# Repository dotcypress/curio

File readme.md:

# Curio

Glorified Infrared Remote Control.

## Resources

- [Schematics](docs/curio.pdf)
- [Gerber files](docs/curio_pcb_rev_0x02.zip)
- [Interactive BOM](https://htmlpreview.github.io/?https://github.com/dotcypress/curio/blob/main/docs/ibom.html)
- [Rust firmware](https://github.com/dotcypress/curio-firmware)

## Credits

* [`1-Bit Icons`](https://vectorpixelstar.itch.io) by VectorPixelStar
* [`Edition 12`](https://www.dafont.com/edition-12.font) font by Designer's High
* [`BM Army`](https://www.dafont.com/bm-army.font) font by BitmapMania
* [`Nokia Cellphone FC`](https://www.dafont.com/nokia-cellphone.font) font by Zeh Fernando

## License

Licensed under either of

- Apache License, Version 2.0 ([LICENSE-APACHE](LICENSE-APACHE) or
  http://www.apache.org/licenses/LICENSE-2.0)
- MIT license ([LICENSE-MIT](LICENSE-MIT) or http://opensource.org/licenses/MIT)

at your option.

### Contribution

Unless you explicitly state otherwise, any contribution intentionally submitted
for inclusion in the work by you, as defined in the Apache-2.0 license, shall be
dual licensed as above, without any additional terms or conditions.

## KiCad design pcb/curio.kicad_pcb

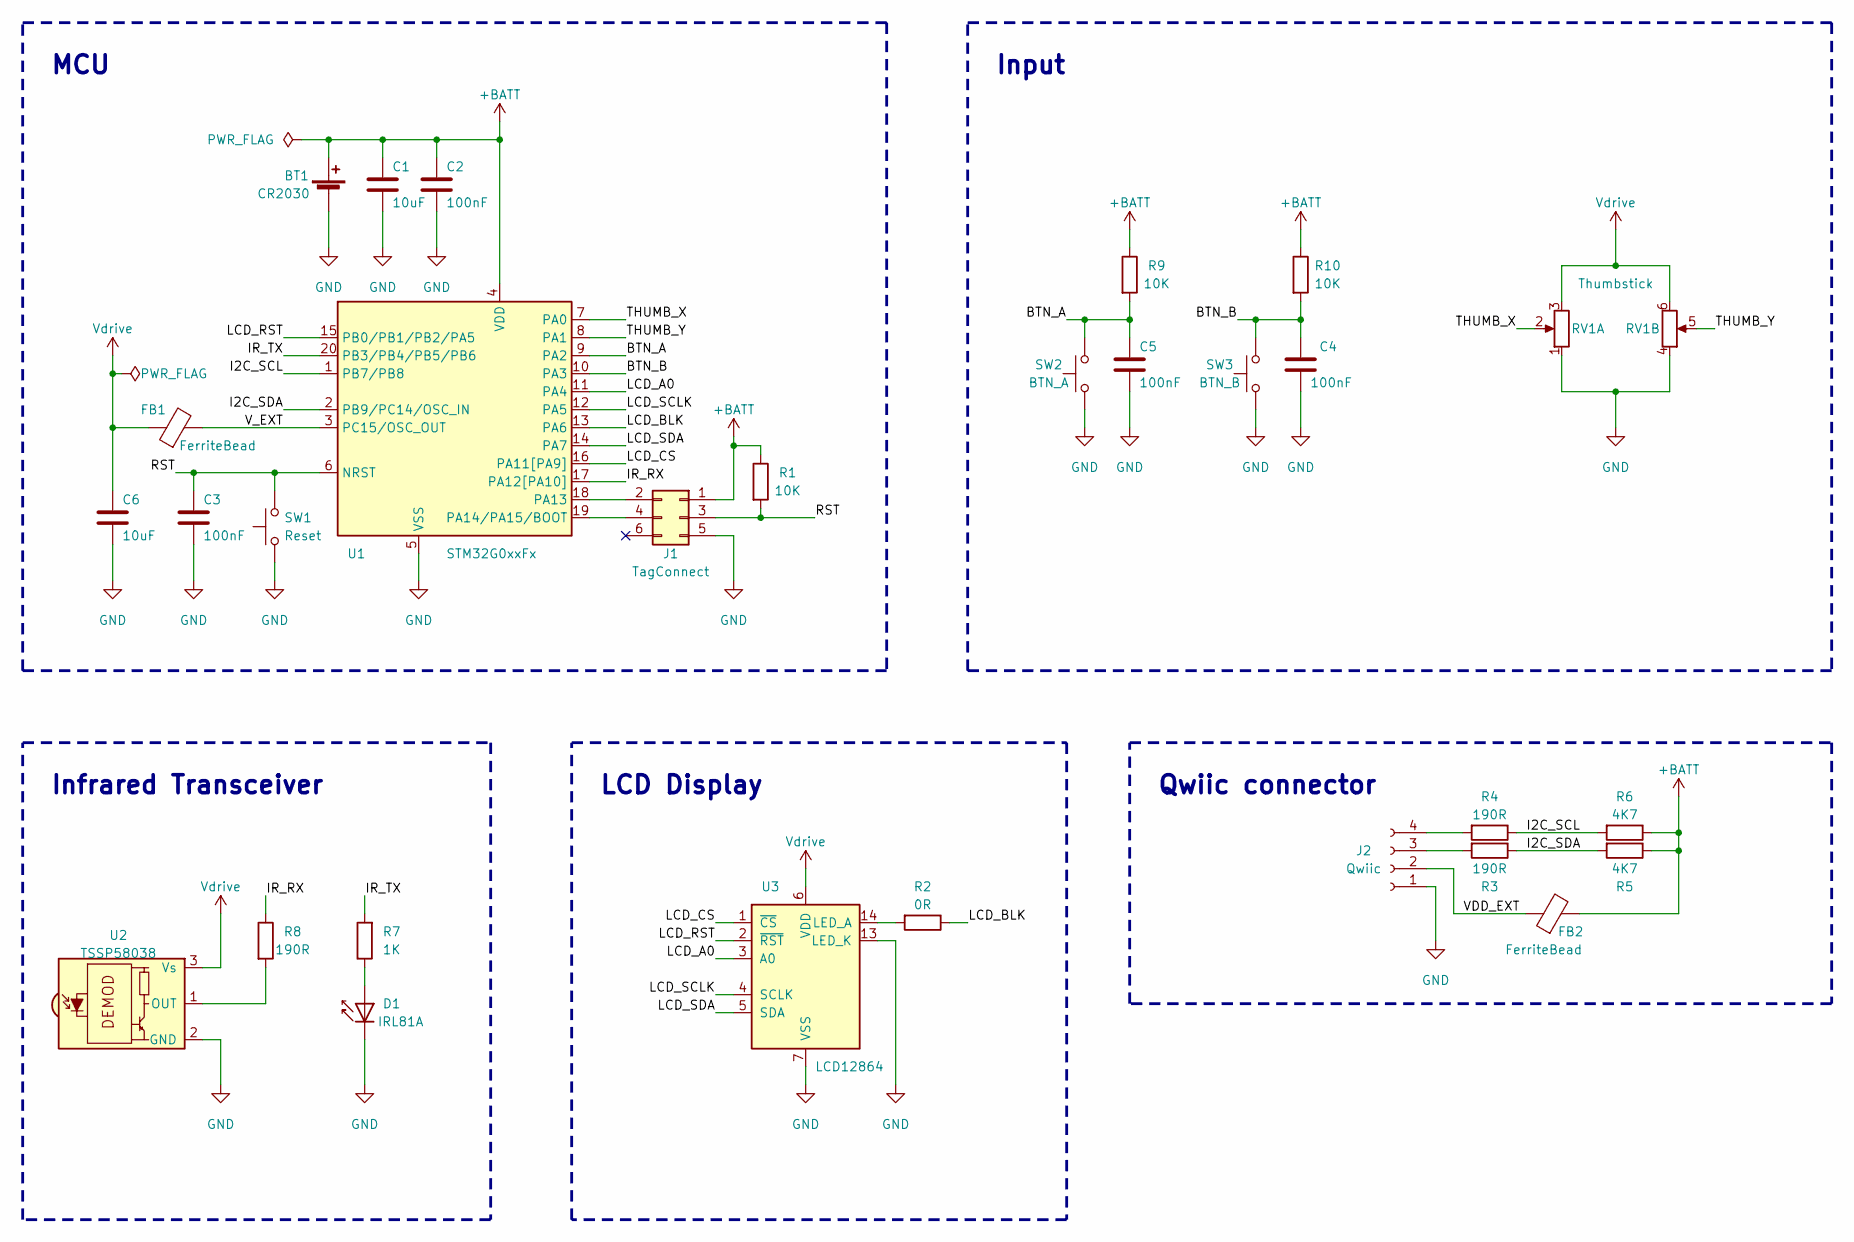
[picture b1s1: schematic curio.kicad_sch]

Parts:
BT1: CR2030; BatteryHolder-Lynx-BAT-HLD-001
C1, C6: 10uF; C_0603_1608Metric
C2, C3, C4, C5: 100nF; C_0603_1608Metric
D1: IRL81A; LED_SideEmitter_Rectangular_W4.5mm_H1.6mm
FB1, FB2: FerriteBead; R_0603_1608Metric
J1: TagConnect; Tag-Connect_TC2030-IDC-NL_2x03_P1.27mm_Vertical
J2: Qwiic; JST_SH_SM04B-SRSS-TB_1x04-1MP_P1.00mm_Horizontal
R1, R9, R10: 10K; R_0603_1608Metric
R2: 0R; R_0603_1608Metric
R3, R4, R8: 190R; R_0603_1608Metric
R5, R6: 4K7; R_0603_1608Metric
R7: 1K; R_0603_1608Metric
RV1: Thumbstick
SW1: Reset; R_1206_3216Metric_Pad1.30x1.75mm_HandSolder
SW2: BTN_A; SW_DIP_SPSTx01_Slide_6.7x4.1mm_W6.73mm_P2.54mm_LowProfile_J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
SW3: BTN_B; SW_DIP_SPSTx01_Slide_6.7x4.1mm_W6.73mm_P2.54mm_LowProfile_J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
U1: STM32G0xxFx; TSSOP-20_4.4x6.5mm_P0.65mm
U2: TSSP58038; Vishay_MINICAST-3Pin
U3: LCD12864; LCD_FPC_1x14_P0.80mm

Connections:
+BATT: BT1.1 (+), C1.1, C2.1, FB2.2, J1.1, R1.1, R5.1, R6.1, R9.1, R10.1, U1.4 (VDD)
/BTN_A: C5.1, R9.2, SW2.2, U1.9 (PA2)
/BTN_B: C4.1, R10.2, SW3.2, U1.10 (PA3)
/I2C_SCL: R4.1, R6.2, U1.1 (PB7/PB8)
/I2C_SDA: R3.1, R5.2, U1.2 (PB9/PC14/OSC_IN)
/IR_RX: R8.1, U1.17 (PA12[PA10])
/IR_TX: R7.2, U1.20 (PB3/PB4/PB5/PB6)
/LCD_A0: U1.11 (PA4), U3.3 (A0)
/LCD_BLK: R2.1, U1.13 (PA6)
/LCD_CS: U1.16 (PA11[PA9]), U3.1 (~CS)
/LCD_RST: U1.15 (PB0/PB1/PB2/PA5), U3.2 (~RST)
/LCD_SCLK: U1.12 (PA5), U3.4 (SCLK)
/LCD_SDA: U1.14 (PA7), U3.5 (SDA)
/RST: C3.1, J1.3, R1.2, SW1.2, U1.6 (NRST)
/THUMB_X: RV1.2, U1.7 (PA0)
/THUMB_Y: RV1.5, U1.8 (PA1)
/VDD_EXT: FB2.1, J2.2
/V_EXT: FB1.2, U1.3 (PC15/OSC_OUT)
GND: BT1.2 (-), C1.2, C2.2, C3.2, C4.2, C5.2, C6.2, D1.1 (K), J1.5, J2.1, RV1.1, RV1.4, SW1.1, SW2.1, SW3.1, U1.5 (VSS), U2.2 (GND), U3.7 (VSS), U3.13 (LED_K)
unnamed: D1.2 (A), R7.1
unnamed: J1.2, U1.18 (PA13)
unnamed: J1.4, U1.19 (PA14/PA15/BOOT)
unnamed: J2.3, R3.2
unnamed: J2.4, R4.2
unnamed: R8.2, U2.1 (OUT)
unnamed: R2.2, U3.14 (LED_A)
Vdrive: C6.1, FB1.1, RV1.3, RV1.6, U2.3 (Vs), U3.6 (VDD)

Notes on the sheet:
Input
MCU
Qwiic connector
LCD Display
Infrared Transceiver

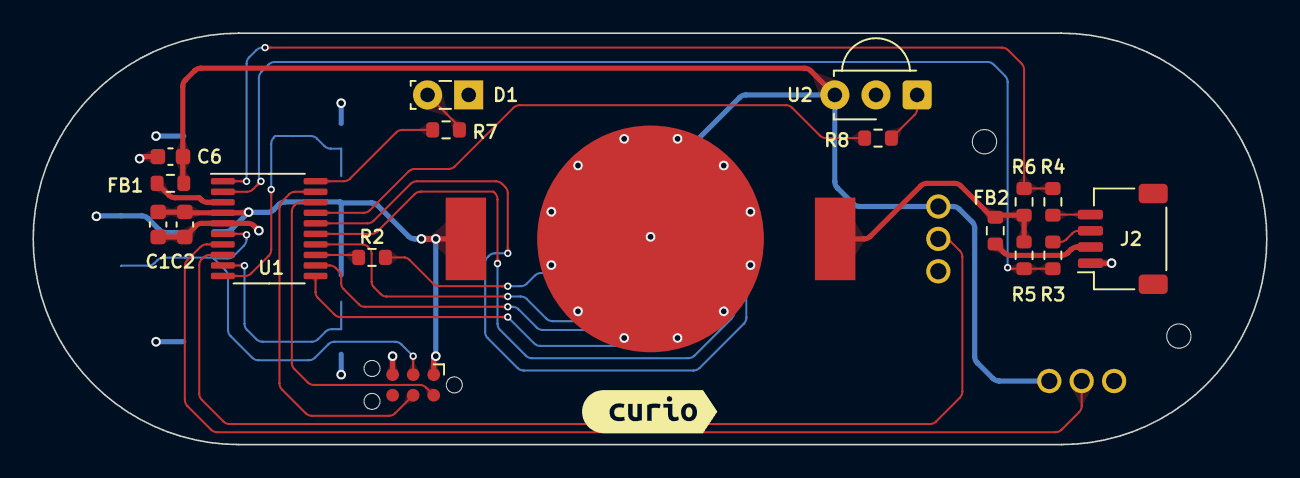
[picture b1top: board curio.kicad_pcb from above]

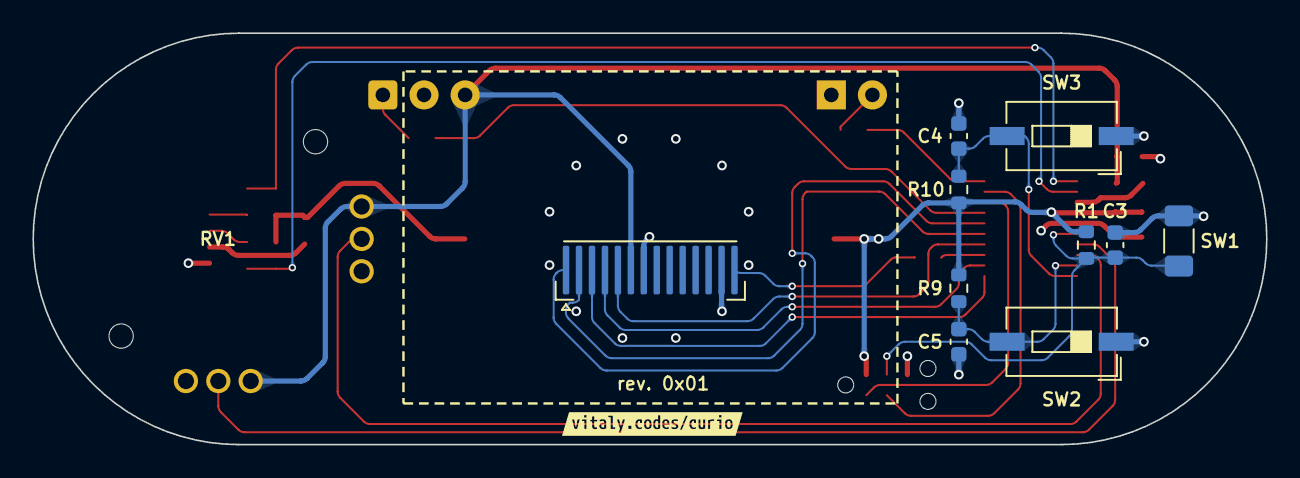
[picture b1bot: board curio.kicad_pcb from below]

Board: 4 copper layers, 76.2 x 25.4 mm, 31 parts (12 on the bottom side), 27 nets.

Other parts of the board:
kibuzzard-633E88B5: G***; kibuzzard-633E88B5
kibuzzard-633E88FC: G***; kibuzzard-633E88FC

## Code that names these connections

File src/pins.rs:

use crate::hal::gpio::{gpioa::*, gpiob::*, gpioc::*};
use hal::gpio::{DefaultMode, Floating, Input, OpenDrain, Output, PushPull};
use hal::prelude::*;
use hal::rcc::Rcc;
use hal::stm32::*;

// Qwiic I2C
pub type I2cClk = PB8<Output<OpenDrain>>;
pub type I2cSda = PB9<Output<OpenDrain>>;

// Display
pub type LcdDC = PA4<Output<PushPull>>;
pub type LcdCS = PA11<Output<PushPull>>;
pub type LcdReset = PB0<Output<PushPull>>;
pub type LcdClk = PA5<DefaultMode>;
pub type LcdSda = PA7<DefaultMode>;
pub type LcdBacklight = PA6<DefaultMode>;

// Infared
pub type IrTx = PB6<DefaultMode>;
pub type IrRx = PA12<Input<Floating>>;

// Buttons
pub type ButtonA = PA2<Input<Floating>>;
pub type ButtonB = PA3<Input<Floating>>;

// Thumb
pub type ThumbX = PA1<DefaultMode>;
pub type ThumbY = PA0<DefaultMode>;

// DisplayPower
pub type DisplayPower = PC15<Output<PushPull>>;

// SWD
pub type SwdIo = PA13<DefaultMode>;
pub type SwdClk = PA14<DefaultMode>;

pub struct Pins {
    // SWD
    pub swd_io: SwdIo,
    pub swd_clk: SwdClk,

    // Qwiic I2C
    pub i2c_clk: I2cClk,
    pub i2c_sda: I2cSda,

    // Display
    pub lcd_reset: LcdReset,
    pub lcd_dc: LcdDC,
    pub lcd_cs: LcdCS,
    pub lcd_clk: LcdClk,
    pub lcd_sda: LcdSda,
    pub lcd_backlight: LcdBacklight,

    // Infared
    pub ir_tx: IrTx,
    pub ir_rx: IrRx,

    // Buttons
    pub btn_a: ButtonA,
    pub btn_b: ButtonB,

    // Thumb
    pub thumb_x: ThumbX,
    pub thumb_y: ThumbY,

    // Power
    pub lcd_power: DisplayPower,
}

impl Pins {
    pub fn new(gpioa: GPIOA, gpiob: GPIOB, gpioc: GPIOC, rcc: &mut Rcc) -> Self {
        let port_a = gpioa.split(rcc);
        let port_b = gpiob.split(rcc);
        let port_c = gpioc.split(rcc);

        Self {
            // SWD
            swd_io: port_a.pa13,
            swd_clk: port_a.pa14,

            // Qwiic I2C
            i2c_clk: port_b.pb8.into_open_drain_output_in_state(PinState::High),
            i2c_sda: port_b.pb9.into_open_drain_output_in_state(PinState::High),

            // Display
            lcd_reset: port_b.pb0.into(),
            lcd_dc: port_a.pa4.into(),
            lcd_cs: port_a.pa11.into(),
            lcd_clk: port_a.pa5,
            lcd_sda: port_a.pa7,
            lcd_backlight: port_a.pa6,

            // Infared
            ir_tx: port_b.pb6,
            ir_rx: port_a.pa12.into(),

            // Buttons
            btn_a: port_a.pa2.into(),
            btn_b: port_a.pa3.into(),

            // Thumb
            thumb_y: port_a.pa0,
            thumb_x: port_a.pa1,

            // Display Power
            lcd_power: port_c.pc15.into(),
        }
    }
}

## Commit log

2022-10-06 rev.0x01
2022-10-14 rev 0x02
2022-10-15 update bom
2022-10-15 rev. 0x02
2022-10-15 fix thumb readings
2022-10-16 change backlight range
2022-10-16 update pcb photo
2022-10-17 updat wireframes
2022-10-18 update control/display
2022-10-19 update klaptik
2022-10-19 thumb type
2022-11-06 ir samplerate config
2022-11-08 update IR mode
2022-11-15 update deps
2023-01-14 update klaptik version
2023-01-20 update hal version
